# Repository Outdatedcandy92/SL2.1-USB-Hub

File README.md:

# SL2.1S USB Hub

A compact USB 2.0 hub that uses the SL2.1S and MCP2221AxML. The board features 1 USB Type-C upstream port and 8 downstream ports with 4 Type-A and 4 Type-C ports, Two of the Type-A ports act as a UART-to-USB and I2C-to-USB bridge.

To use this USB Hub, simply plug the USB-C port that's on the right side to your host device. This USB Hub requires no firmware or drivers and should work by default on all operating systems.

---

## Schematics

The project's KiCad files can be found under `/PCB/kicad`.

---

## PCB

---

## BOM

| Name          | Description                                                                | Quantity | Price  | Shipping  |
| ------------- | -------------------------------------------------------------------------- | -------- | ------ | --------- |
| Componenets   | Componenets from LCSC. detailed part breakdown [here](/production/bom.csv) | -        | $10.40 | $12.64+$3 |
| PCB+Stencil   | PCB and Stencil from JLCPCB                                                | -        | $7     | $8.84     |
| **Sub Total** |                                                                            |          | $17.40 | $24.48    |
| **Total**     |                                                                            |          | $41.88 |           |

---

## License

This project is licensed under the CERN Open Hardware Licence Version 2 Weakly Reciprocal [(CERN OHL W)](LICENSE.txt)

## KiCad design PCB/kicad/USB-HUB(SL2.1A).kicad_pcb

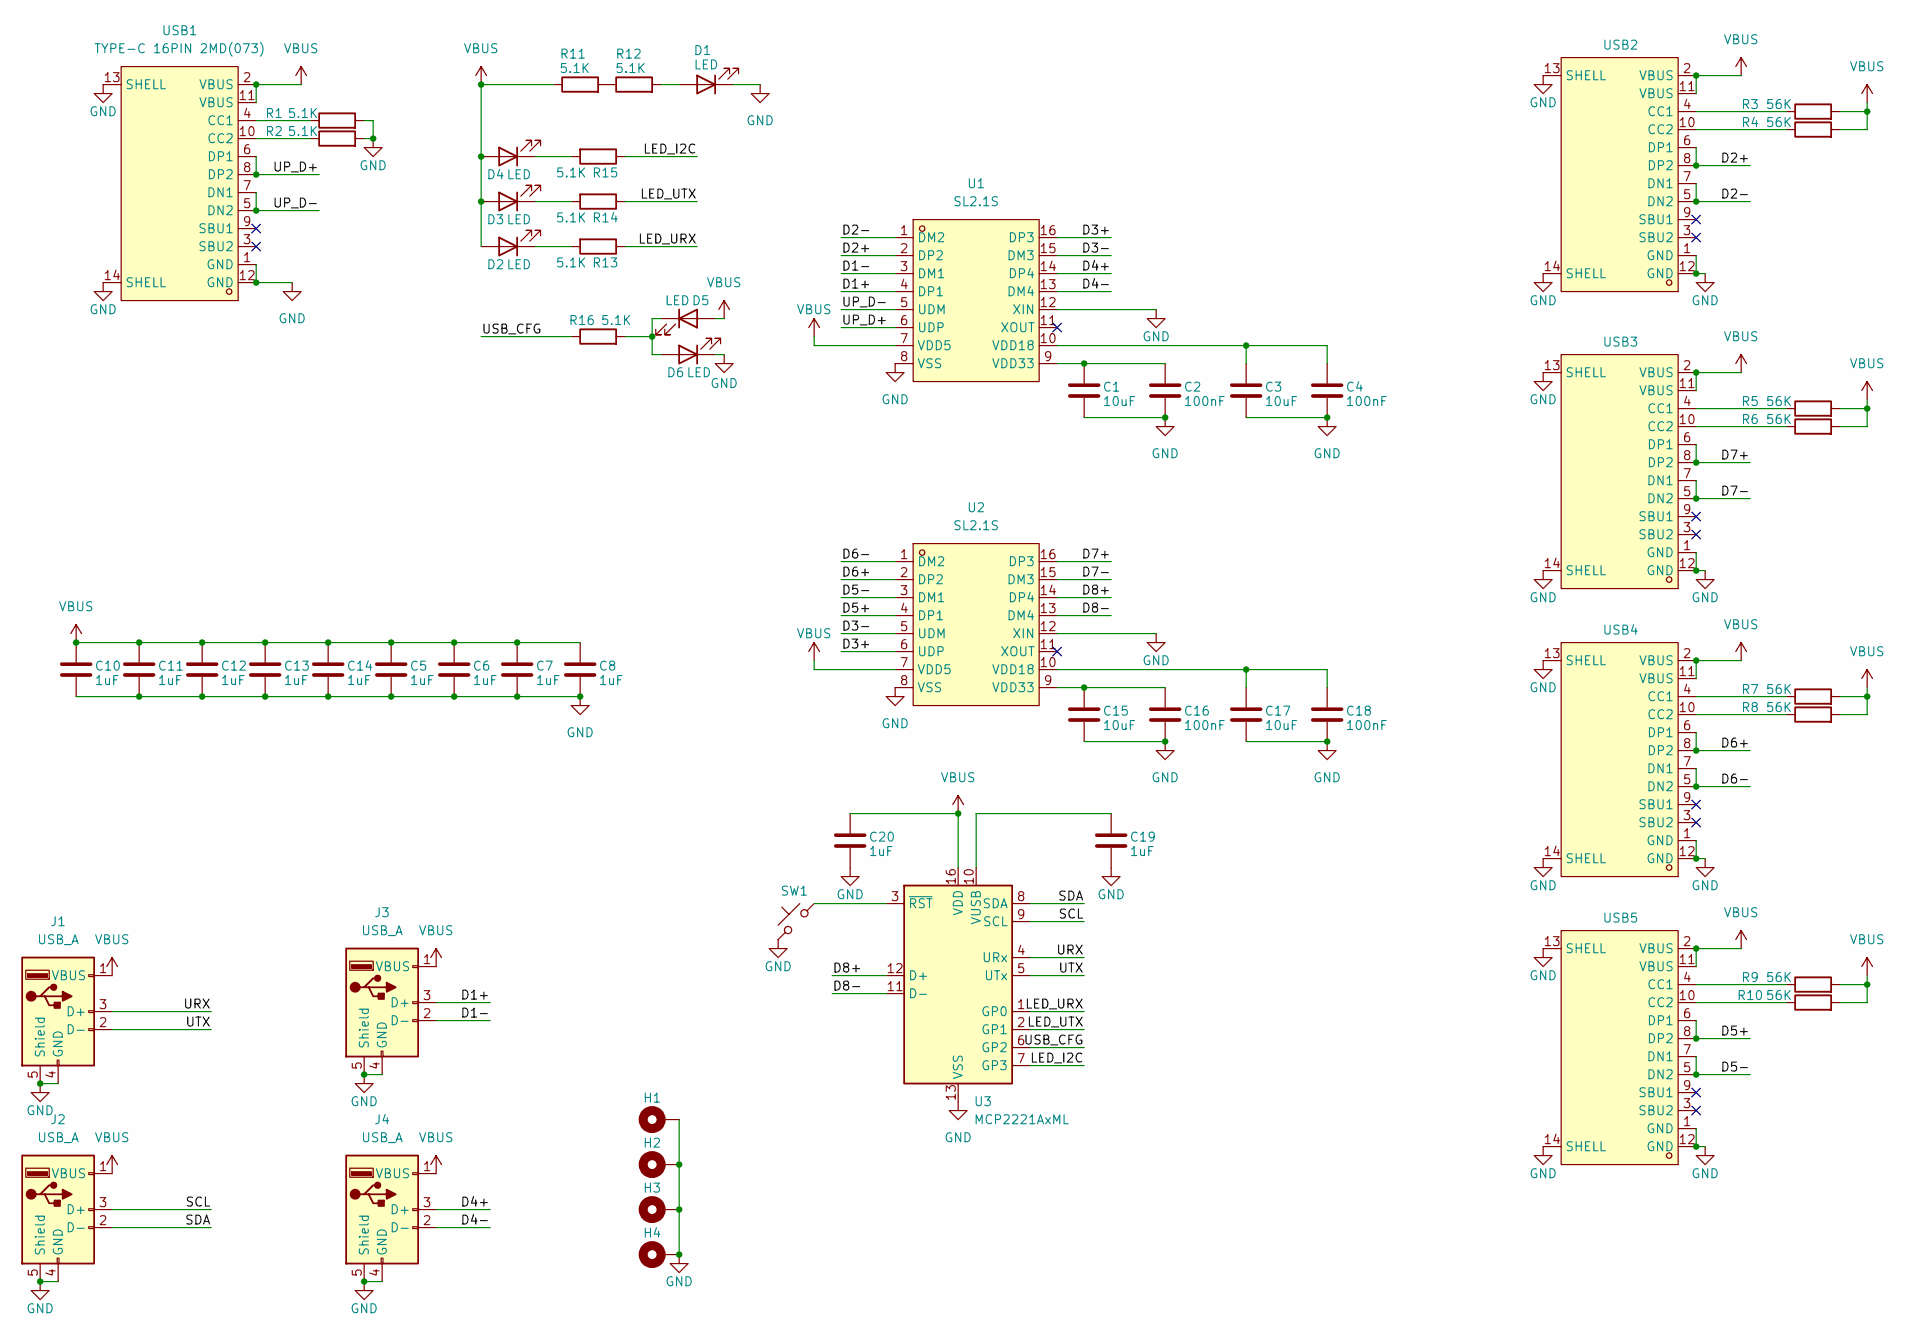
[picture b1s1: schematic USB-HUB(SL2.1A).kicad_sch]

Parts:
C1, C3, C15, C17: 10uF; C_0402_1005Metric; LCSC Part C315248
C2, C4, C16, C18: 100nF; C_0402_1005Metric; LCSC Part C1525
C5, C6, C7, C8, C10, C11, C12, C13, C14, C19, C20: 1uF; C_0402_1005Metric; LCSC Part C14445
D1, D2, D3, D4, D5, D6: LED; LED_0402_1005Metric; LCSC Part C20608784
H1, H2, H3, H4: MountingHole_Pad_MP; MountingHole_2.5mm_Pad_TopBottom
J1, J2, J3, J4: USB_A; USB-A-TH_10.0QHHTZB6.3; LCSC Part C668591
R1, R2, R11, R12, R13, R14, R15, R16: 5.1K; R_0402_1005Metric; LCSC Part C25905
R3, R4, R5, R6, R7, R8, R9, R10: 56K; R_0402_1005Metric; LCSC Part C25796
SW1: SW_Push_45deg; R_0402_1005Metric
U1, U2: SL2.1S; SSOP-16_L4.6-W2.6-P0.53-LS4.0-BL; LCSC Part C2684433
U3: MCP2221AxML; QFN-16-1EP_4x4mm_P0.65mm_EP2.5x2.5mm; LCSC Part C637690
USB1, USB2, USB3, USB4, USB5: TYPE-C 16PIN 2MD(073); USB-C-SMD_TYPE-C-6PIN-2MD-073; LCSC Part C2765186

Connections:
/D1+: J3.3 (D+), U1.4 (DP1)
/D1-: J3.2 (D-), U1.3 (DM1)
/D2+: U1.2 (DP2), USB2.6 (DP1), USB2.8 (DP2)
/D2-: U1.1 (DM2), USB2.5 (DN2), USB2.7 (DN1)
/D3+: U1.16 (DP3), U2.6 (UDP)
/D3-: U1.15 (DM3), U2.5 (UDM)
/D4+: J4.3 (D+), U1.14 (DP4)
/D4-: J4.2 (D-), U1.13 (DM4)
/D5+: U2.4 (DP1), USB5.6 (DP1), USB5.8 (DP2)
/D5-: U2.3 (DM1), USB5.5 (DN2), USB5.7 (DN1)
/D6+: U2.2 (DP2), USB4.6 (DP1), USB4.8 (DP2)
/D6-: U2.1 (DM2), USB4.5 (DN2), USB4.7 (DN1)
/D7+: U2.16 (DP3), USB3.6 (DP1), USB3.8 (DP2)
/D7-: U2.15 (DM3), USB3.5 (DN2), USB3.7 (DN1)
/D8+: U2.14 (DP4), U3.12 (D+)
/D8-: U2.13 (DM4), U3.11 (D-)
/LED_I2C: R15.1, U3.7 (GP3)
/LED_URX: R13.1, U3.1 (GP0)
/LED_UTX: R14.1, U3.2 (GP1)
/SCL: J2.3 (D+), U3.9 (SCL)
/SDA: J2.2 (D-), U3.8 (SDA)
/UP_D+: U1.6 (UDP), USB1.6 (DP1), USB1.8 (DP2)
/UP_D-: U1.5 (UDM), USB1.5 (DN2), USB1.7 (DN1)
/URX: J1.3 (D+), U3.4 (URx)
/USB_CFG: R16.1, U3.6 (GP2)
/UTX: J1.2 (D-), U3.5 (UTx)
GND: C1.2, C2.2, C3.2, C4.2, C5.2, C6.2, C7.2, C8.2, C10.2, C11.2, C12.2, C13.2, C14.2, C15.2, C16.2, C17.2, C18.2, C19.2, C20.2, D1.1 (K), D6.1 (K), H1.MP, H2.MP, H3.MP, H4.MP, J1.4 (GND), J1.5 (Shield), J2.4 (GND), J2.5 (Shield), J3.4 (GND), J3.5 (Shield), J4.4 (GND), J4.5 (Shield), R1.2, R2.2, SW1.2, U1.8 (VSS), U1.12 (XIN), U2.8 (VSS), U2.12 (XIN), U3.13 (VSS), USB1.1 (GND), USB1.12 (GND), USB1.13 (SHELL), USB1.14 (SHELL), USB2.1 (GND), USB2.12 (GND), USB2.13 (SHELL), USB2.14 (SHELL), USB3.1 (GND), USB3.12 (GND), USB3.13 (SHELL), USB3.14 (SHELL), USB4.1 (GND), USB4.12 (GND), USB4.13 (SHELL), USB4.14 (SHELL), USB5.1 (GND), USB5.12 (GND), USB5.13 (SHELL), USB5.14 (SHELL)
unnamed: D1.2 (A), R12.2
unnamed: D2.1 (K), R13.2
unnamed: D3.1 (K), R14.2
unnamed: D4.1 (K), R15.2
unnamed: D5.1 (K), D6.2 (A), R16.2
unnamed: R11.2, R12.1
unnamed: C3.1, C4.1, U1.10 (VDD18)
unnamed: C1.1, C2.1, U1.9 (VDD33)
unnamed: C17.1, C18.1, U2.10 (VDD18)
unnamed: C15.1, C16.1, U2.9 (VDD33)
unnamed: C19.1, U3.10 (VUSB)
unnamed: SW1.1, U3.3 (~RST)
unnamed: R1.1, USB1.4 (CC1)
unnamed: R2.1, USB1.10 (CC2)
unnamed: R3.1, USB2.4 (CC1)
unnamed: R4.1, USB2.10 (CC2)
unnamed: R5.1, USB3.4 (CC1)
unnamed: R6.1, USB3.10 (CC2)
unnamed: R7.1, USB4.4 (CC1)
unnamed: R8.1, USB4.10 (CC2)
unnamed: R9.1, USB5.4 (CC1)
unnamed: R10.1, USB5.10 (CC2)
VBUS: C5.1, C6.1, C7.1, C8.1, C10.1, C11.1, C12.1, C13.1, C14.1, C20.1, D2.2 (A), D3.2 (A), D4.2 (A), D5.2 (A), J1.1 (VBUS), J2.1 (VBUS), J3.1 (VBUS), J4.1 (VBUS), R3.2, R4.2, R5.2, R6.2, R7.2, R8.2, R9.2, R10.2, R11.1, U1.7 (VDD5), U2.7 (VDD5), U3.16 (VDD), USB1.2 (VBUS), USB1.11 (VBUS), USB2.2 (VBUS), USB2.11 (VBUS), USB3.2 (VBUS), USB3.11 (VBUS), USB4.2 (VBUS), USB4.11 (VBUS), USB5.2 (VBUS), USB5.11 (VBUS)

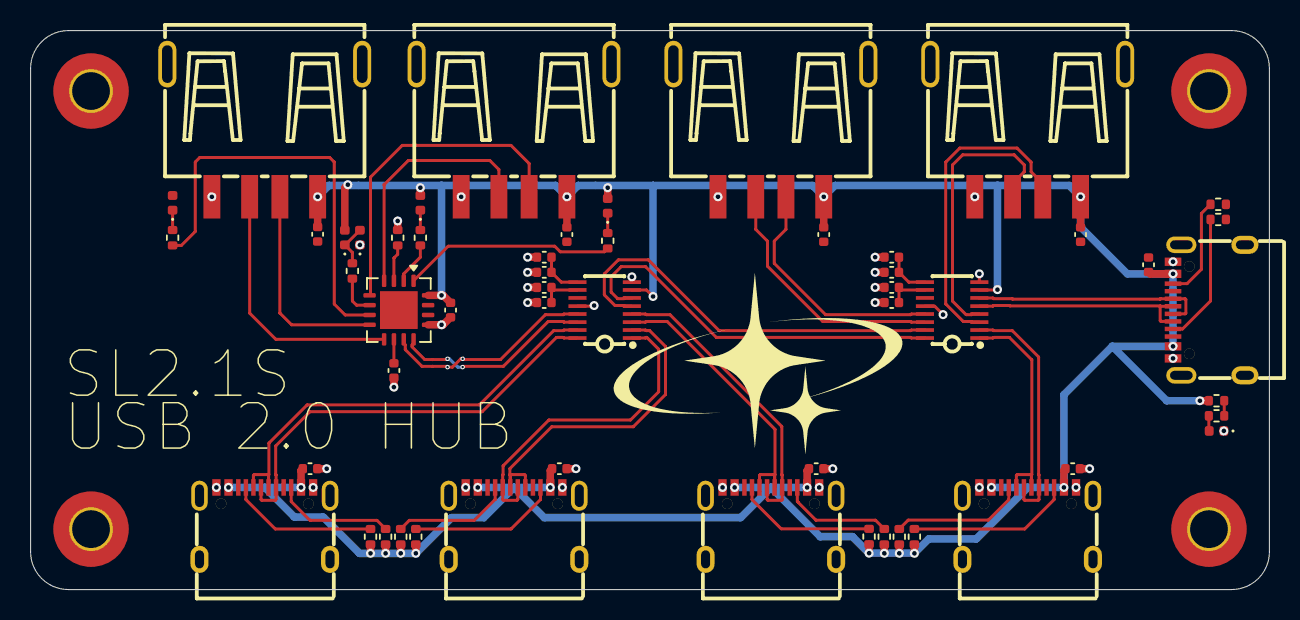
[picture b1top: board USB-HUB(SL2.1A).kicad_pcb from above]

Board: 2 copper layers, 82.0 x 37.0 mm, 58 parts (0 on the bottom side), 50 nets.

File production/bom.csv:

"Reference","Qty","Value","LCSC Part","Footprint"
"C1,C3,C15,C17","4","10uF","C315248","Capacitor_SMD:C_0402_1005Metric"
"C2,C4,C16,C18","4","100nF","C1525","Capacitor_SMD:C_0402_1005Metric"
"C5,C6,C7,C8,C10,C11,C12,C13,C14,C19,C20","11","1uF","C14445","Capacitor_SMD:C_0402_1005Metric"
"D1,D2,D3,D4,D5,D6","6","LED","C20608784","LED_SMD:LED_0402_1005Metric"
"H1,H2,H3,H4","4","MountingHole_Pad_MP","","MountingHole:MountingHole_2.5mm_Pad_TopBottom"
"J1,J2,J3,J4","4","USB_A","C668591","easyeda2kicad:USB-A-TH_10.0QHHTZB6.3"
"R1,R2,R11,R12,R13,R14,R15,R16","8","5.1K","C25905","Resistor_SMD:R_0402_1005Metric"
"R3,R4,R5,R6,R7,R8,R9,R10","8","56K","C25796","Resistor_SMD:R_0402_1005Metric"
"SW1","1","SW_Push_45deg","-","Resistor_SMD:R_0402_1005Metric"
"U1,U2","2","SL2.1S","C2684433","easyeda2kicad:SSOP-16_L4.6-W2.6-P0.53-LS4.0-BL"
"U3","1","MCP2221AxML","C637690","Package_DFN_QFN:QFN-16-1EP_4x4mm_P0.65mm_EP2.5x2.5mm"
"USB1,USB2,USB3,USB4,USB5","5","TYPE-C 16PIN 2MD(073)","C2765186","easyeda2kicad:USB-C-SMD_TYPE-C-6PIN-2MD-073"

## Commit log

2025-12-28 rev 1
2025-12-28 added board .step file
2026-01-10 rev 2.0
2026-01-29 change cdn
2026-01-29 readme update
2026-03-28 notice
